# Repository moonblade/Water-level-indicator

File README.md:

# Water level indicator

[https://moonblade.github.io/blog/2021/09/11/over-engineering.html](https://moonblade.github.io/blog/2021/09/11/over-engineering.html)

A nodemcu tied to an ultrasonic sensor detects the distance to the water level at every ten seconds and uploads it to a firebase realtime db.

Android app, takes data from this db, and calculates current percentage based on min and max values it can have. Outlier values are discarded.

The app widget didn't really function as I wanted it to, so took a second nodemcu and created a water level indicator that takes data from firebase rtdb and displays it on an led matrix.

As an experiment in 3d printing and pcb printing, added eagle board schematic to print the water level indicator on pcb. Will end up removing the indicator and wire it up to relays to auto control the motor when water level is low.

### Update 2021-09-05

Bought a waterproof ultrasonic sensor, but the version supplied by the manufactorer seems to have some faults. One the minimum distance is too high and two it was giving random readings and not accurate ones. Which makes it unusable for this project. So ended up buying a new normal ultrasonic sensor and gave the waterproof one for return. But to learn previous lessons, figured would keep the sensor on top of the lid this time around so that corrosion doesn't play that big a role and it would be impossible for it to fall into water.

To that end, drilled a couple of holes in the lid of the water tank and stuck the sensor through it covering most of it with insulation tape. Also overhauled the microchip so that its easily replacable and works directly off of ac power doing its own coversion instead of relying on a phone charger.

Old vs new

Underside of lid

Topside connected up

### Update 2021-09-01 

The water level sensor was connected to the lid of hte water tank by threading it through the lid. The thread broke and the full box took a dip in the water and fried the electronics.
Till then it was getting a ton of water droplets on it due to evaporation as well. So the board looks really gnarly due to that.

For the updated version, will be using waterproof ultrasonic sensor and the ic will be kept seperate and not inside the lid anymore.

## Arduino code

### WaterLevelIndicator

Take data from firebase rtdb and display it on an 8x8 LED matrix based on value of printMode.

Installed in kitchen

### WaterLevelSensor

Get distance to water level and upload it to firebase rtdb.

Installed on the underside of the water tank lid. Had to do some rewiring of the electrical connections in the roof to provide uninterupted power bypassing a switch.

## App Screenshots

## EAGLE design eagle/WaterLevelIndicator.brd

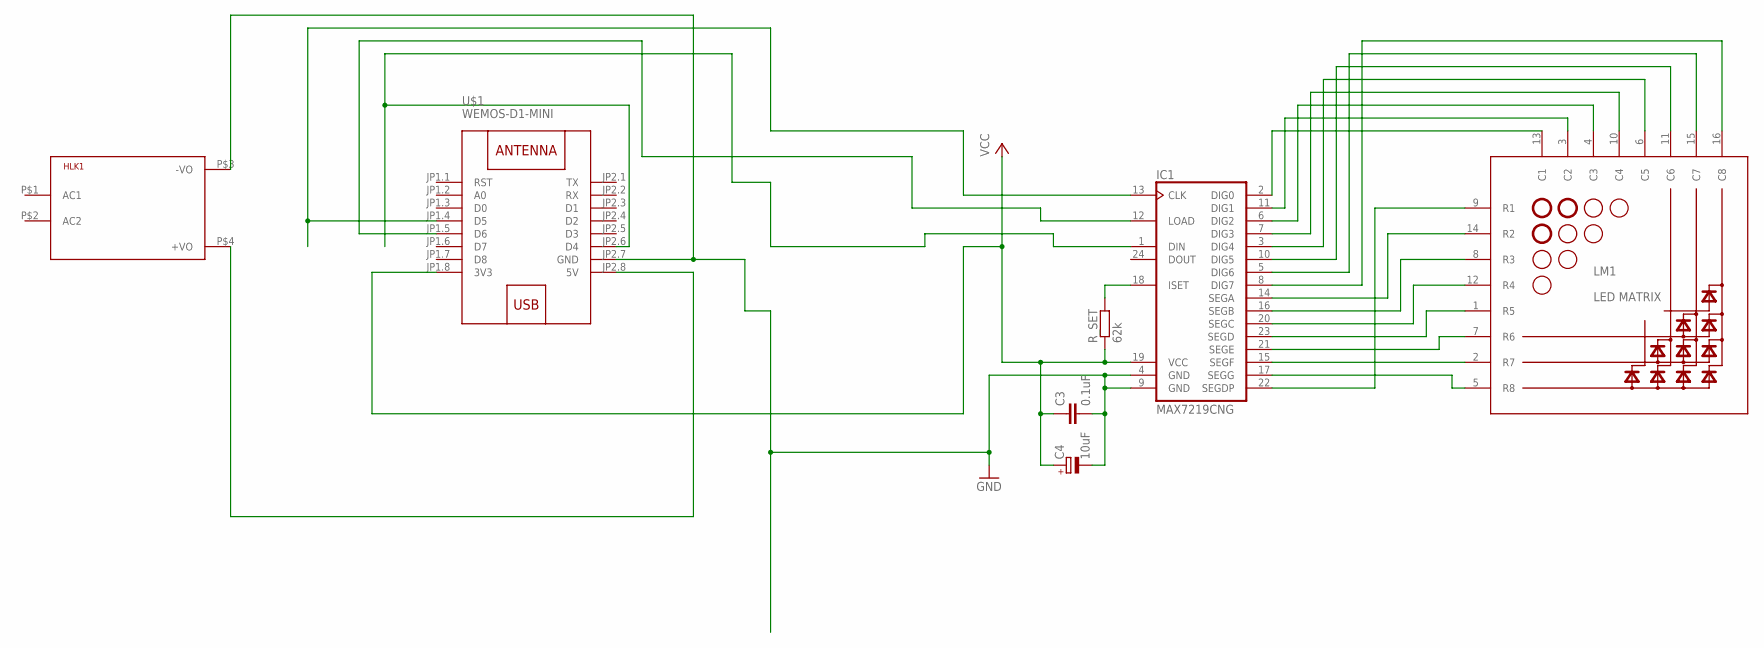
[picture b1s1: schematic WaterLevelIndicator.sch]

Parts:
C3: 0.1uF; C025-024X044
C4: 10uF; E2-5
HLK1: HLK-PM013W; HLK-PM01
IC1: MAX7219CNG; DIL24-3
LM1: LED MATRIX; LED_MATRIX
R_SET: 62k; 0207/10
U$1: WEMOS-D1-MINI

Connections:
GND: C3.2, C4.-, HLK1.P$3 (-VO), IC1.4 (GND), IC1.9 (GND), U$1.JP2.7 (GND)
unnamed: HLK1.P$4 (+VO), U$1.JP2.8 (5V)
unnamed: IC1.15 (SEGF), LM1.2 (R7)
unnamed: IC1.1 (DIN), U$1.JP2.6 (D4)
unnamed: IC1.12 (LOAD), U$1.JP1.5 (D6)
unnamed: IC1.13 (CLK), U$1.JP1.4 (D5)
unnamed: IC1.21 (SEGE), LM1.7 (R6)
unnamed: IC1.23 (SEGD), LM1.1 (R5)
unnamed: IC1.20 (SEGC), LM1.12 (R4)
unnamed: IC1.16 (SEGB), LM1.8 (R3)
unnamed: IC1.14 (SEGA), LM1.14 (R2)
unnamed: IC1.22 (SEGDP), LM1.9 (R1)
unnamed: IC1.8 (DIG7), LM1.16 (C8)
unnamed: IC1.5 (DIG6), LM1.15 (C7)
unnamed: IC1.10 (DIG5), LM1.11 (C6)
unnamed: IC1.3 (DIG4), LM1.6 (C5)
unnamed: IC1.7 (DIG3), LM1.10 (C4)
unnamed: IC1.6 (DIG2), LM1.4 (C3)
unnamed: IC1.11 (DIG1), LM1.3 (C2)
unnamed: IC1.2 (DIG0), LM1.13 (C1)
unnamed: IC1.18 (ISET), R_SET.2
unnamed: IC1.17 (SEGG), LM1.5 (R8)
VCC: C3.1, C4.+, IC1.19 (VCC), R_SET.1, U$1.JP1.8 (3V3)

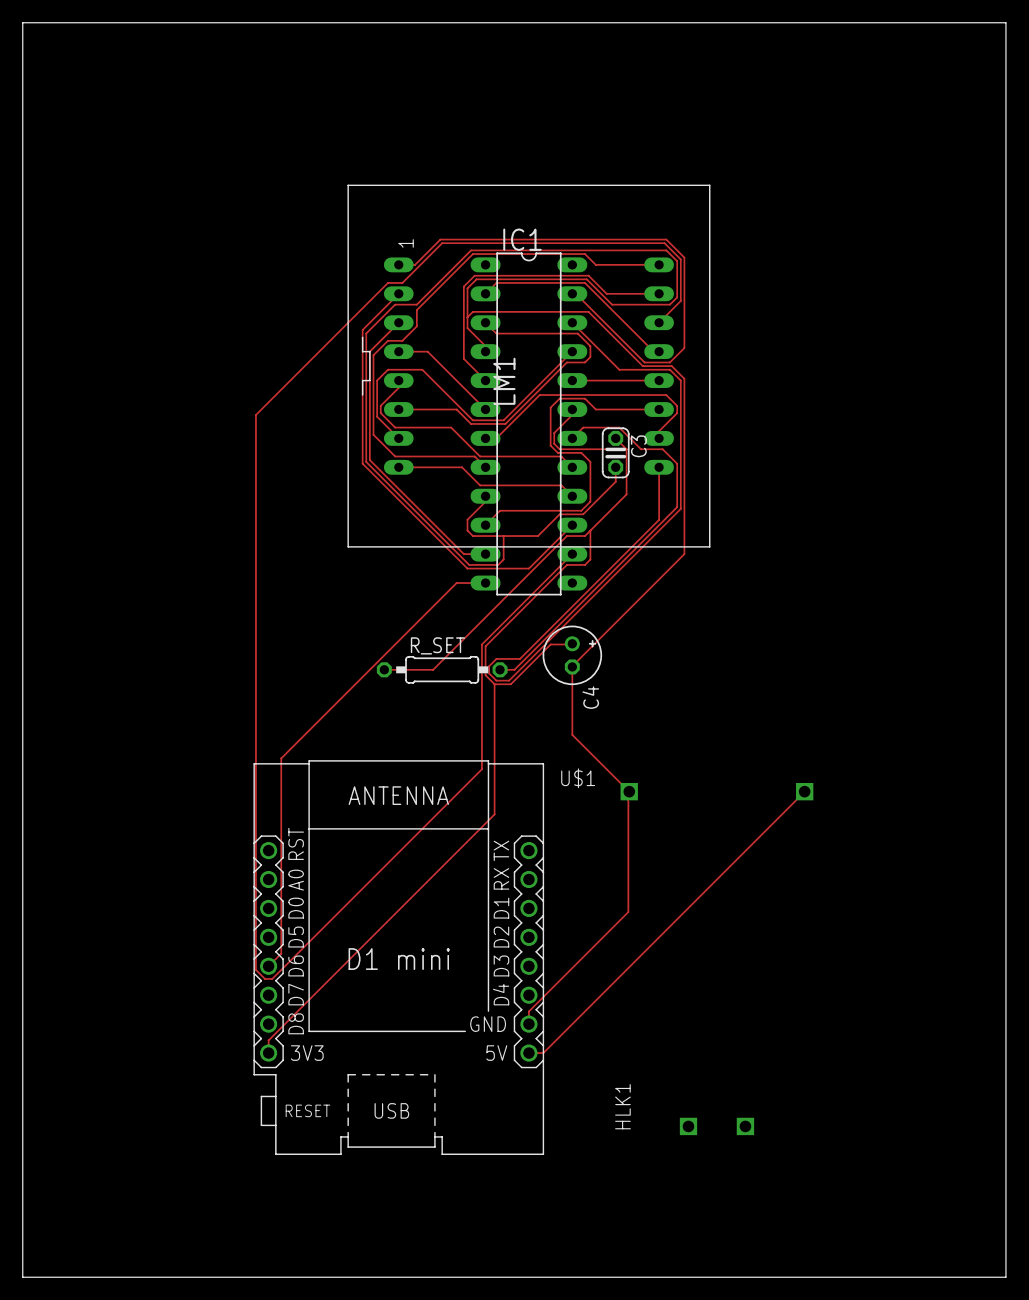
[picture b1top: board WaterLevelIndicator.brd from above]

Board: 2 copper layers, 86.3 x 110.2 mm, 7 parts (0 on the bottom side), 23 nets.

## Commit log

2021-02-13 init
2021-02-13 Auto updating settings activity
2021-02-13 Updated values correctly now
2021-03-05 add nodemcu code as well
2021-03-05 screenshots
2021-03-05 screenshot
2021-03-07 modifications
2021-03-11 update node scripts
2021-03-11 Add toggles in app
2021-03-21 updated creds
2021-05-02 add boards
2021-05-03 added eagle schematics
2021-05-03 more boards
2021-05-03 current
2021-05-03 more optimization
2021-05-03 add holes
2021-05-04 need to add two jumpers
2021-05-04 new board
2021-05-05 final board?
2021-05-29 Modification to readme
2021-07-22 Modify it to directly take percentage from firebase
2021-08-09 Update indicator even if rpi is down and percentage is not updated
2021-09-03 Update on broken sensor
2021-09-03 typo
2021-09-13 Direct mode wasn\'t working, fixes that
2021-09-15 Add auto update over ota code into the water level indicator fore remote updates
2021-09-16 minor update to check working of auto updater
2021-09-16 Add auto update code to sensor as well
2021-09-16 Update logic to take average of ten entries
2021-09-16 Simplify indicator code
2021-09-16 Add mode calculation for more stability
2021-09-25 sample code from arduino
2021-09-25 temp
2021-10-02 Test
2021-10-02 Got it to work with waterproof sensor, finally

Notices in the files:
parts and their libraries:
diy-modules: Released under the Creative Commons Attribution 4.0 International License: http://creativecommons.org/licenses/by/4.0
